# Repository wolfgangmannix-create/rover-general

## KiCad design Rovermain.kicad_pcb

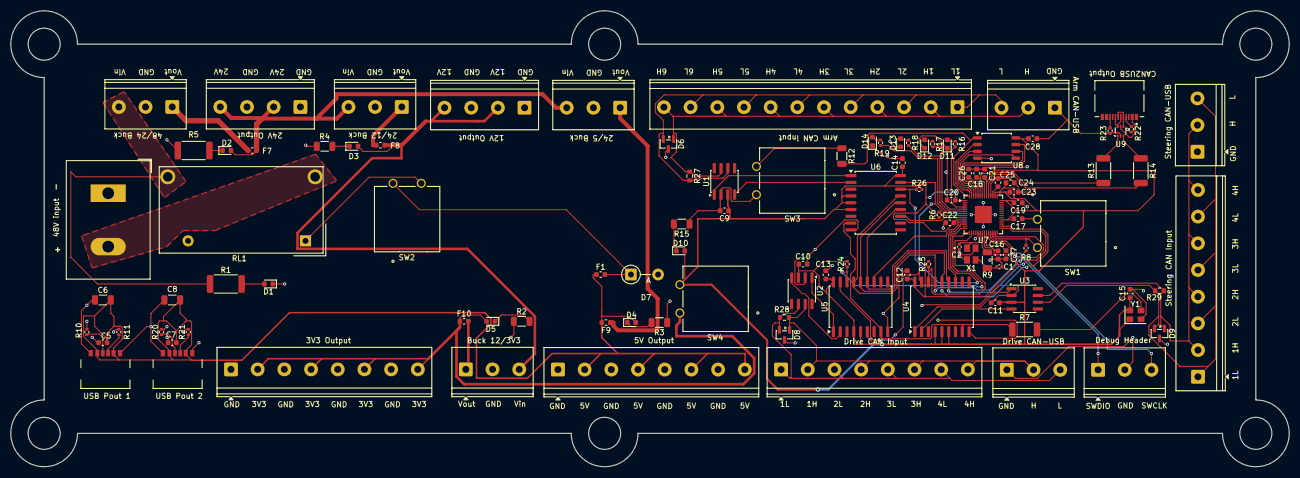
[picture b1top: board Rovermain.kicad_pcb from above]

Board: 2 copper layers, 239.5 x 85.4 mm, 109 parts (0 on the bottom side), 79 nets.

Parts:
C1, C2: 15pf; C_0402_1005Metric
C5, C7, C9, C10, C11, C12, C13, C14, C15, C16, C17, C18, C19, C20, C21, C22, C23, C26, C27, C28: .1uF; C_0603_1608Metric
C6, C8: 10uF; C_1206_3216Metric
C24, C25: 1uF; C_0603_1608Metric
D1, D2, D3, D4, D5, D10, D11, D12, D13, D14: LED; LED_0603_1608Metric
D6, D8, D9: NUP2105L; SOT-23
D7: D; D_DO-41_SOD81_P5.08mm_Vertical_AnodeUp
F1: Fuse_Small; Fuse_0603_1608Metric
F7, F8, F9, F10: Fuse; Fuse_0603_1608Metric
J1: 48V input; TerminalBlock_Dinkle_DT-55-B01X-02_P10.00mm
J2: USB_C_Receptacle_Pi_Power; 2171750001_MOL
J3: 24V Output; TerminalBlock_Phoenix_PT-1,5-4-5.0-H_1x04_P5.00mm_Horizontal
J4: USB_C_Receptacle_Spare_power; 2171750001_MOL
J5: Buck 48/24; TerminalBlock_Phoenix_PT-1,5-3-5.0-H_1x03_P5.00mm_Horizontal
J6: Buck 24/12; TerminalBlock_Phoenix_PT-1,5-3-5.0-H_1x03_P5.00mm_Horizontal
J7: Buck 24/5; TerminalBlock_Phoenix_PT-1,5-3-5.0-H_1x03_P5.00mm_Horizontal
J8: Buck 12/3V3; TerminalBlock_Phoenix_PT-1,5-3-5.0-H_1x03_P5.00mm_Horizontal
J9: 12V Output; TerminalBlock_Phoenix_PT-1,5-4-5.0-H_1x04_P5.00mm_Horizontal
J10: 3V3 Output; TerminalBlock_Phoenix_PT-1,5-8-5.0-H_1x08_P5.00mm_Horizontal
J11: 5V Output; TerminalBlock_Phoenix_PT-1,5-8-5.0-H_1x08_P5.00mm_Horizontal
J12: Arm CAN-USB; TerminalBlock_Phoenix_PT-1,5-3-5.0-H_1x03_P5.00mm_Horizontal
J13: Drive CAN-USB; TerminalBlock_Phoenix_PT-1,5-3-5.0-H_1x03_P5.00mm_Horizontal
J14: Steering CAN-USB; TerminalBlock_Phoenix_PT-1,5-3-5.0-H_1x03_P5.00mm_Horizontal
J15: Drive CAN Input; TerminalBlock_Phoenix_PT-1,5-8-5.0-H_1x08_P5.00mm_Horizontal
J16: Steering CAN Input; TerminalBlock_Phoenix_PT-1,5-8-5.0-H_1x08_P5.00mm_Horizontal
J17: Arm CAN Input; TerminalBlock_Phoenix_PT-1,5-12-5.0-H_1x12_P5.00mm_Horizont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
J18: Debug Header; TerminalBlock_Phoenix_PT-1,5-3-5.0-H_1x03_P5.00mm_Horizontal
J19: USB_C_Receptacle_CAN; CONN_8p94X6p5X3p16_12L_GCC
R1: 22kOhm; R_2512_6332Metric
R2: 150Ohm; R_1206_3216Metric
R3: 330Ohm; R_1206_3216Metric
R4, R9, R12, R15: 1kOhm; R_1206_3216Metric
R5: 2.7kOhm; R_2512_6332Metric
R6, R8, R24, R25, R26: 10kOhm; R_0402_1005Metric
R7, R13, R14: 27Ohm; R_2010_5025Metric
R10, R11, R20, R21, R22, R23: 5.1kohm (1pct); R_0402_1005Metric
R16, R17, R18, R19: 330Ohm; R_0402_1005Metric
R27, R28, R29: 120Ohm; R_0603_1608Metric
RL1: AZDC007; Relay_SPST_Zettler-AZSR131
SW1: SW_Push; SWITCH_03211B
SW2: SW_Push_Open; SWITCH_03211B
SW3: BOOTSEL; SWITCH_03211B
SW4: CAN2USB_Enable; SWITCH_03211B
U1, U2, U3: SN65HVD232; SOIC-8_3.9x4.9mm_P1.27mm
U4, U5, U6: MCP2515-xSO; SOIC-18W_7.5x11.6mm_P1.27mm
U7: RP2040; QFN-56-1EP_7x7mm_P0.4mm_EP3.2x3.2mm
U8: W25Q16JVSS; SOIC-8_5.3x5.3mm_P1.27mm
U9: USBLC6-2P6; SOT-666
X1: ABM8-272-T3; ABM8-272-T3_ABR
Y1: ASE-16MHz; Oscillator_SMD_Abracon_ASE-4Pin_3.2x2.5mm

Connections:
+3v3: D5.2 (A), F10.1, J10.2, J10.4, J10.6, J10.8, SW4.1 (1_1)
+3v3IC: C9.1, C10.1, C11.1, C12.1, C13.1, C14.1, C15.1, C16.2, C17.2, C18.2, C19.2, C20.2, C21.2, C22.2, C23.2, C24.2, C28.1, D10.2 (A), R6.2, R8.2, R24.2, R25.2, R26.2, SW4.6, U1.3 (VCC), U2.3 (VCC), U3.3 (VCC), U4.4 (~TX0RTS), U4.5 (~TX1RTS), U4.6 (~TX2RTS), U4.18 (VDD), U5.4 (~TX0RTS), U5.5 (~TX1RTS), U5.6 (~TX2RTS), U5.18 (VDD), U6.4 (~TX0RTS), U6.5 (~TX1RTS), U6.6 (~TX2RTS), U6.18 (VDD), U7.1 (IOVDD), U7.10 (IOVDD), U7.22 (IOVDD), U7.33 (IOVDD), U7.42 (IOVDD), U7.43 (ADC_AVDD), U7.44 (VREG_VIN), U7.48 (USB_VDD), U7.49 (IOVDD), U8.8 (VCC), Y1.1 (EN), Y1.4 (Vdd)
/12V: D3.2 (A), F8.2, J8.3, J9.2, J9.4
/24V: D2.2 (A), F7.2, J3.2, J3.4, J6.3, J7.3
/48V: J5.3, R1.1, RL1.13
/+5V: C5.1, C6.2, C7.1, C8.2, D4.2 (A), F1.1, F9.2, J2.A9 (VBUS), J2.B9 (VBUS), J4.A9 (VBUS), J4.B9 (VBUS), J11.2, J11.4, J11.6, J11.8
/AH: D6.1 (K), J12.2, J17.2, J17.4, J17.6, J17.8, J17.10, J17.12, R27.1, U1.7 (CANH)
/AL: D6.2 (K), J12.3, J17.1, J17.3, J17.5, J17.7, J17.9, J17.11, R27.2, U1.6 (CANL)
/CAN2USB/+1v1: C25.2, C26.2, C27.2, U7.23 (DVDD), U7.45 (VREG_VOUT), U7.50 (DVDD)
/CAN2USB/ACS: R26.1, U6.16 (~CS), U7.14 (GPIO11)
/CAN2USB/Clock: U4.13 (SCK), U5.13 (SCK), U6.13 (SCK), U7.29 (GPIO18)
/CAN2USB/DCS: R24.1, U5.16 (~CS), U7.15 (GPIO12)
/CAN2USB/GPIO2: R16.2, U7.4 (GPIO2)
/CAN2USB/GPIO3: R17.1, U7.5 (GPIO3)
/CAN2USB/GPIO4: R18.1, U7.6 (GPIO4)
/CAN2USB/GPIO5: R19.1, U7.7 (GPIO5)
/CAN2USB/GRPRES: R6.1, U4.17 (~RESET), U5.17 (~RESET), U6.17 (~RESET), U7.8 (GPIO6)
/CAN2USB/INTA: U6.12 (~INT), U7.9 (GPIO7)
/CAN2USB/INTD: U5.12 (~INT), U7.11 (GPIO8)
/CAN2USB/INTS: U4.12 (~INT), U7.12 (GPIO9)
/CAN2USB/MISO: U4.15 (SO), U5.15 (SO), U6.15 (SO), U7.27 (GPIO16)
/CAN2USB/MOSI: U4.14 (SI), U5.14 (SI), U6.14 (SI), U7.30 (GPIO19)
/CAN2USB/OSCN: R7.2, U4.8 (OSC1), U5.8 (OSC1), U6.8 (OSC1)
/CAN2USB/QSPI_SCLK: U7.52 (QSPI_SCLK), U8.6 (CLK)
/CAN2USB/QSPI_SS: R12.2, U7.56 (~QSPI_SS), U8.1 (~CS)
/CAN2USB/SCS: R25.1, U4.16 (~CS), U7.16 (GPIO13)
/CAN2USB/SD0: U7.53 (QSPI_SD0), U8.5 (DI/IO_{0})
/CAN2USB/SD1: U7.55 (QSPI_SD1), U8.2 (DO/IO_{1})
/CAN2USB/SD2: U7.54 (QSPI_SD2), U8.3 (~WP/IO_{2})
/CAN2USB/SD3: U7.51 (QSPI_SD3), U8.7 (~HOLD/~RESET/IO_{3})
/CAN2USB/USBDN: R14.1, U9.3 (I/O2)
/CAN2USB/USBDP: R13.2, U9.1 (I/O1)
/CAN2USB/VBUSJ19: J19.A4/B9, U9.5 (VBUS)
/CAN2USB/XPIN: C2.1, U7.20 (XIN), X1.1
/CAN2USB/XPOUT: R9.2, U7.21 (XOUT)
/DH: D8.1 (K), J13.2, J15.2, J15.4, J15.6, J15.8, R28.1, U2.7 (CANH)
/DL: D8.2 (K), J13.3, J15.1, J15.3, J15.5, J15.7, R28.2, U2.6 (CANL)
/SH: D9.1 (K), J14.2, J16.2, J16.4, J16.6, J16.8, R29.1, U3.7 (CANH)
/SL: D9.2 (K), J14.3, J16.1, J16.3, J16.5, J16.7, R29.2, U3.6 (CANL)
AD: U1.1 (D), U6.1 (TXCAN)
AR: U1.4 (R), U6.2 (RXCAN)
DD: U2.1 (D), U5.1 (TXCAN)
DR: U2.4 (R), U5.2 (RXCAN)
GNDREF: C1.2, C2.2, C5.2, C6.1, C7.2, C8.1, C9.2, C10.2, C11.2, C12.2, C13.2, C14.2, C15.2, C16.1, C17.1, C18.1, C19.1, C20.1, C21.1, C22.1, C23.1, C24.1, C25.1, C26.1, C27.1, C28.2, D1.1 (K), D6.3 (A), D7.2 (A), D8.3 (A), D9.3 (A), D11.1 (K), D12.1 (K), D13.1 (K), D14.1 (K), J1.1, J2.A12 (GND), J2.B12 (GND), J3.1, J3.3, J4.A12 (GND), J4.B12 (GND), J5.2, J6.2, J7.2, J8.2, J9.1, J9.3, J10.1, J10.3, J10.5, J10.7, J11.1, J11.3, J11.5, J11.7, J12.1, J13.1, J14.1, J18.2, R2.1, R3.1, R4.1, R5.2, R10.2, R11.2, R15.1, R20.2, R21.2, R22.2, R23.2, RL1.A2, SW1.6, SW3.1 (1_1), U1.2 (GND), U2.2 (GND), U3.2 (GND), U4.9 (VSS), U5.9 (VSS), U6.9 (VSS), U7.19 (TESTEN), U7.57 (GND), U8.4 (GND), U9.2 (GND), X1.2, X1.4, Y1.2 (GND)
unnamed: C1.1, R9.1, X1.3
unnamed: D1.2 (A), R1.2
unnamed: D2.1 (K), R5.1
unnamed: D3.1 (K), R4.2
unnamed: D4.1 (K), R3.2
unnamed: D5.1 (K), R2.2
unnamed: D7.1 (K), F1.2, SW2.1 (A_1)
unnamed: D10.1 (K), R15.2
unnamed: D11.2 (A), R16.1
unnamed: D12.2 (A), R17.2
unnamed: D13.2 (A), R18.2
unnamed: D14.2 (A), R19.2
unnamed: J1.2, RL1.14
unnamed: J2.A5 (CC1), R10.1
unnamed: J2.B5 (CC2), R11.1
unnamed: J4.A5 (CC1), R20.1
unnamed: J4.B5 (CC2), R21.1
unnamed: F7.1, J5.1
unnamed: F8.1, J6.1
unnamed: F9.1, J7.1
unnamed: F10.2, J8.1
unnamed: J18.1, U7.25 (SWDIO)
unnamed: J18.3, U7.24 (SWCLK)
unnamed: J19.A5 (CC1), R22.1
unnamed: J19.B5 (CC2), R23.1
unnamed: J19.A6 (D+), J19.B6 (D+), U9.6 (I/O1)
unnamed: J19.A7 (D-), J19.B7 (D-), U9.4 (I/O2)
unnamed: R12.1, SW3.6
unnamed: RL1.A1, SW2.6
unnamed: R8.1, SW1.1 (1_1), U7.26 (RUN)
unnamed: R14.2, U7.46 (USB_DM)
unnamed: R13.1, U7.47 (USB_DP)
unnamed: R7.1, Y1.3 (OUT)
SD: U3.1 (D), U4.1 (TXCAN)
SR: U3.4 (R), U4.2 (RXCAN)
